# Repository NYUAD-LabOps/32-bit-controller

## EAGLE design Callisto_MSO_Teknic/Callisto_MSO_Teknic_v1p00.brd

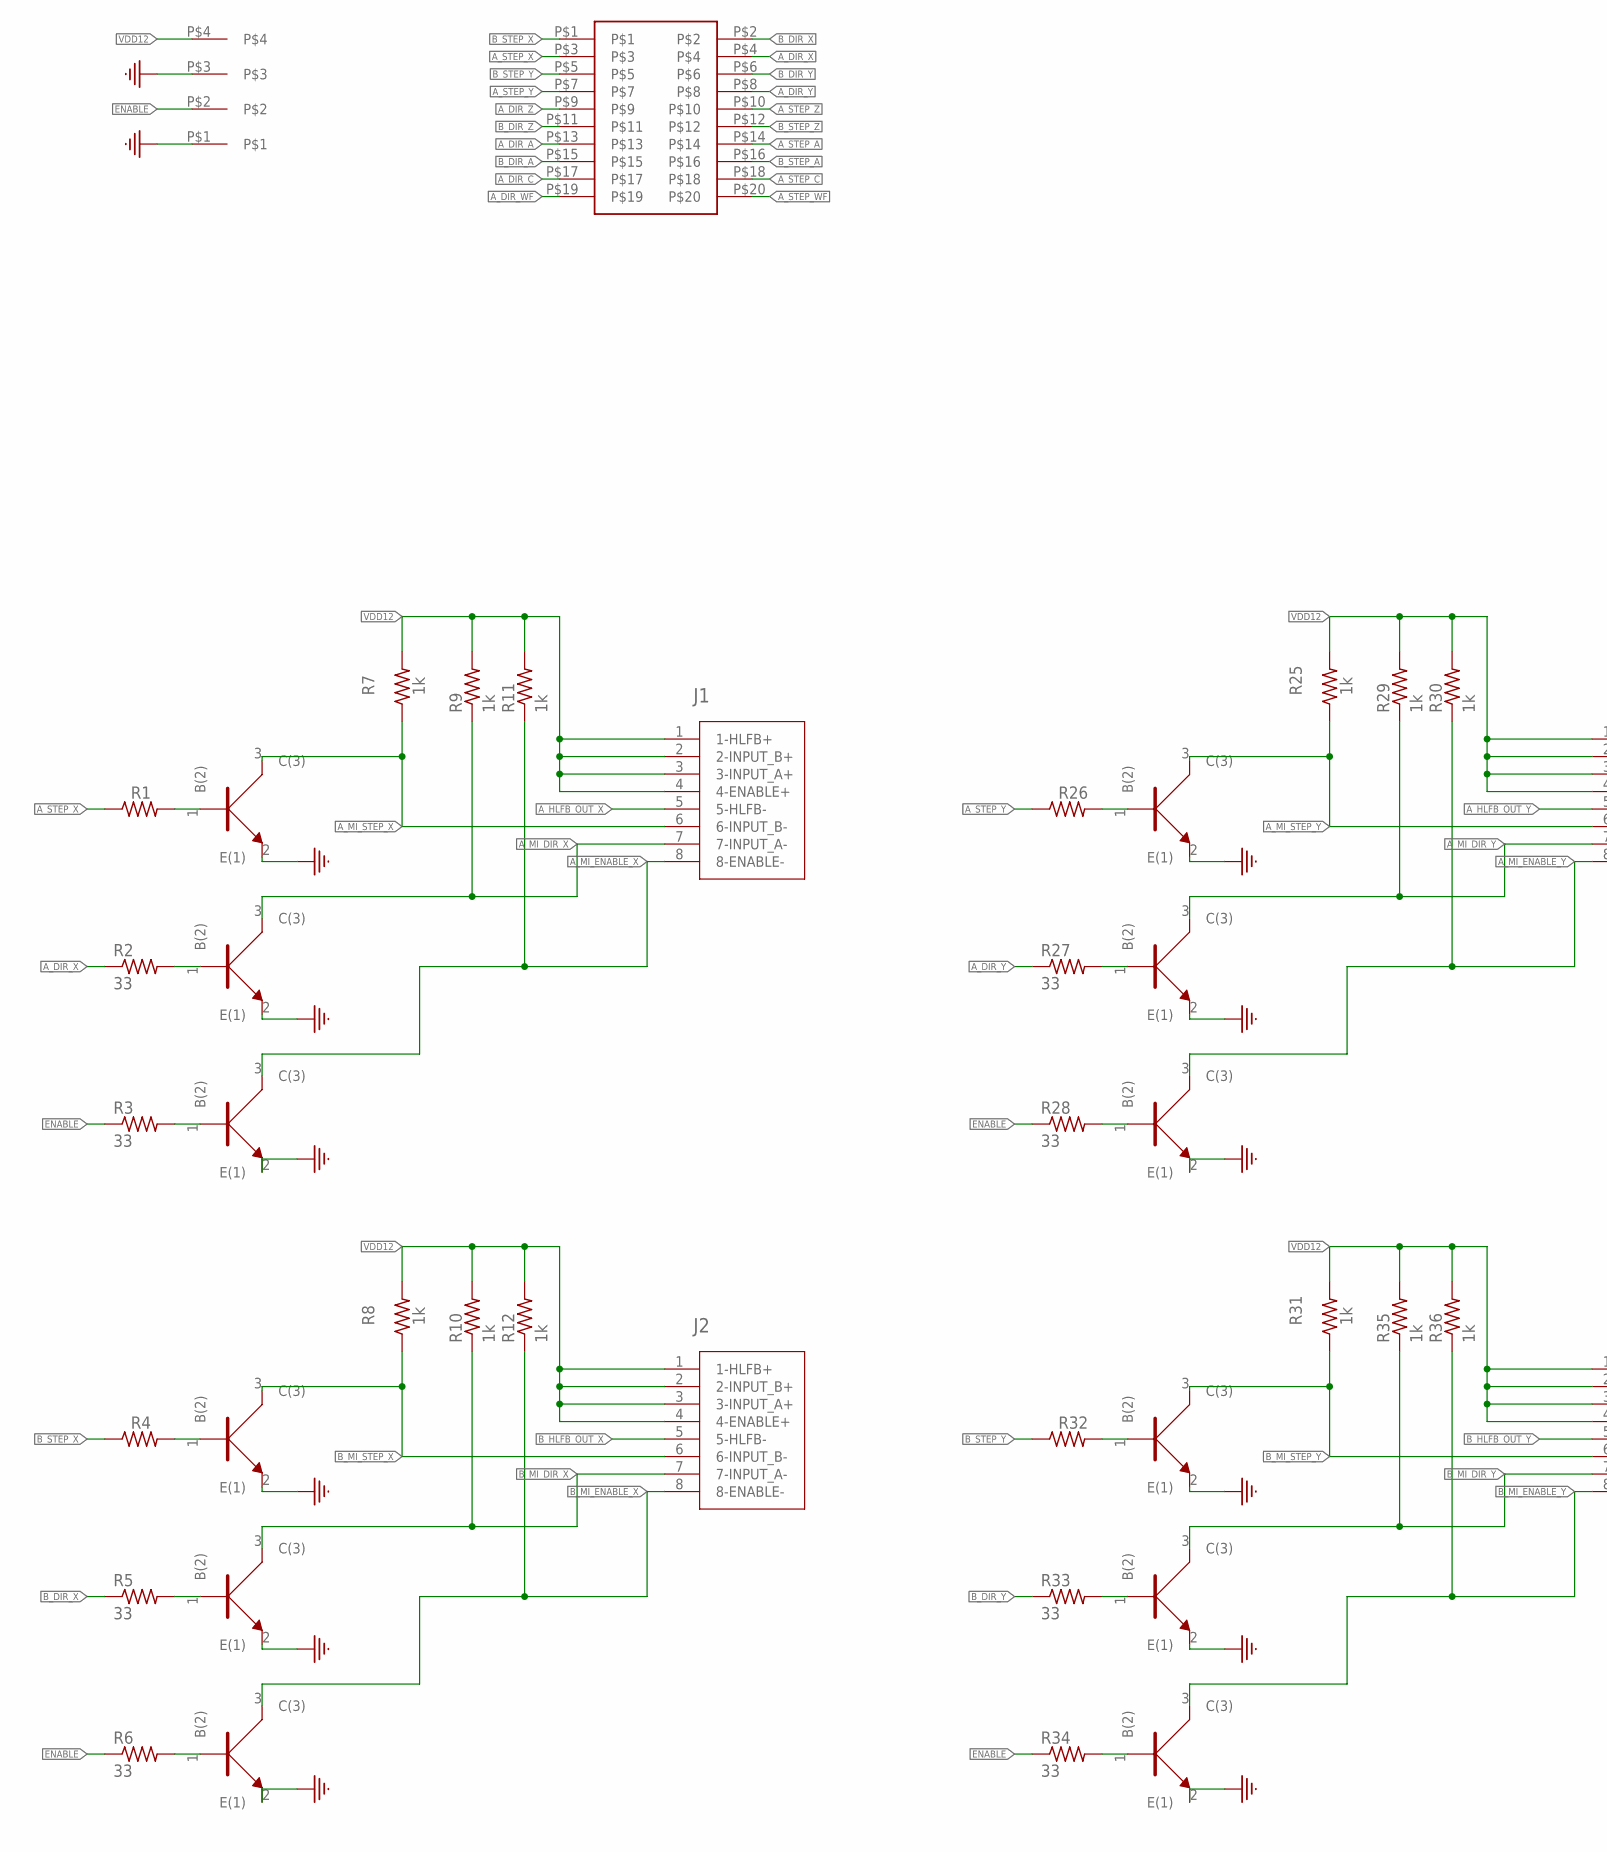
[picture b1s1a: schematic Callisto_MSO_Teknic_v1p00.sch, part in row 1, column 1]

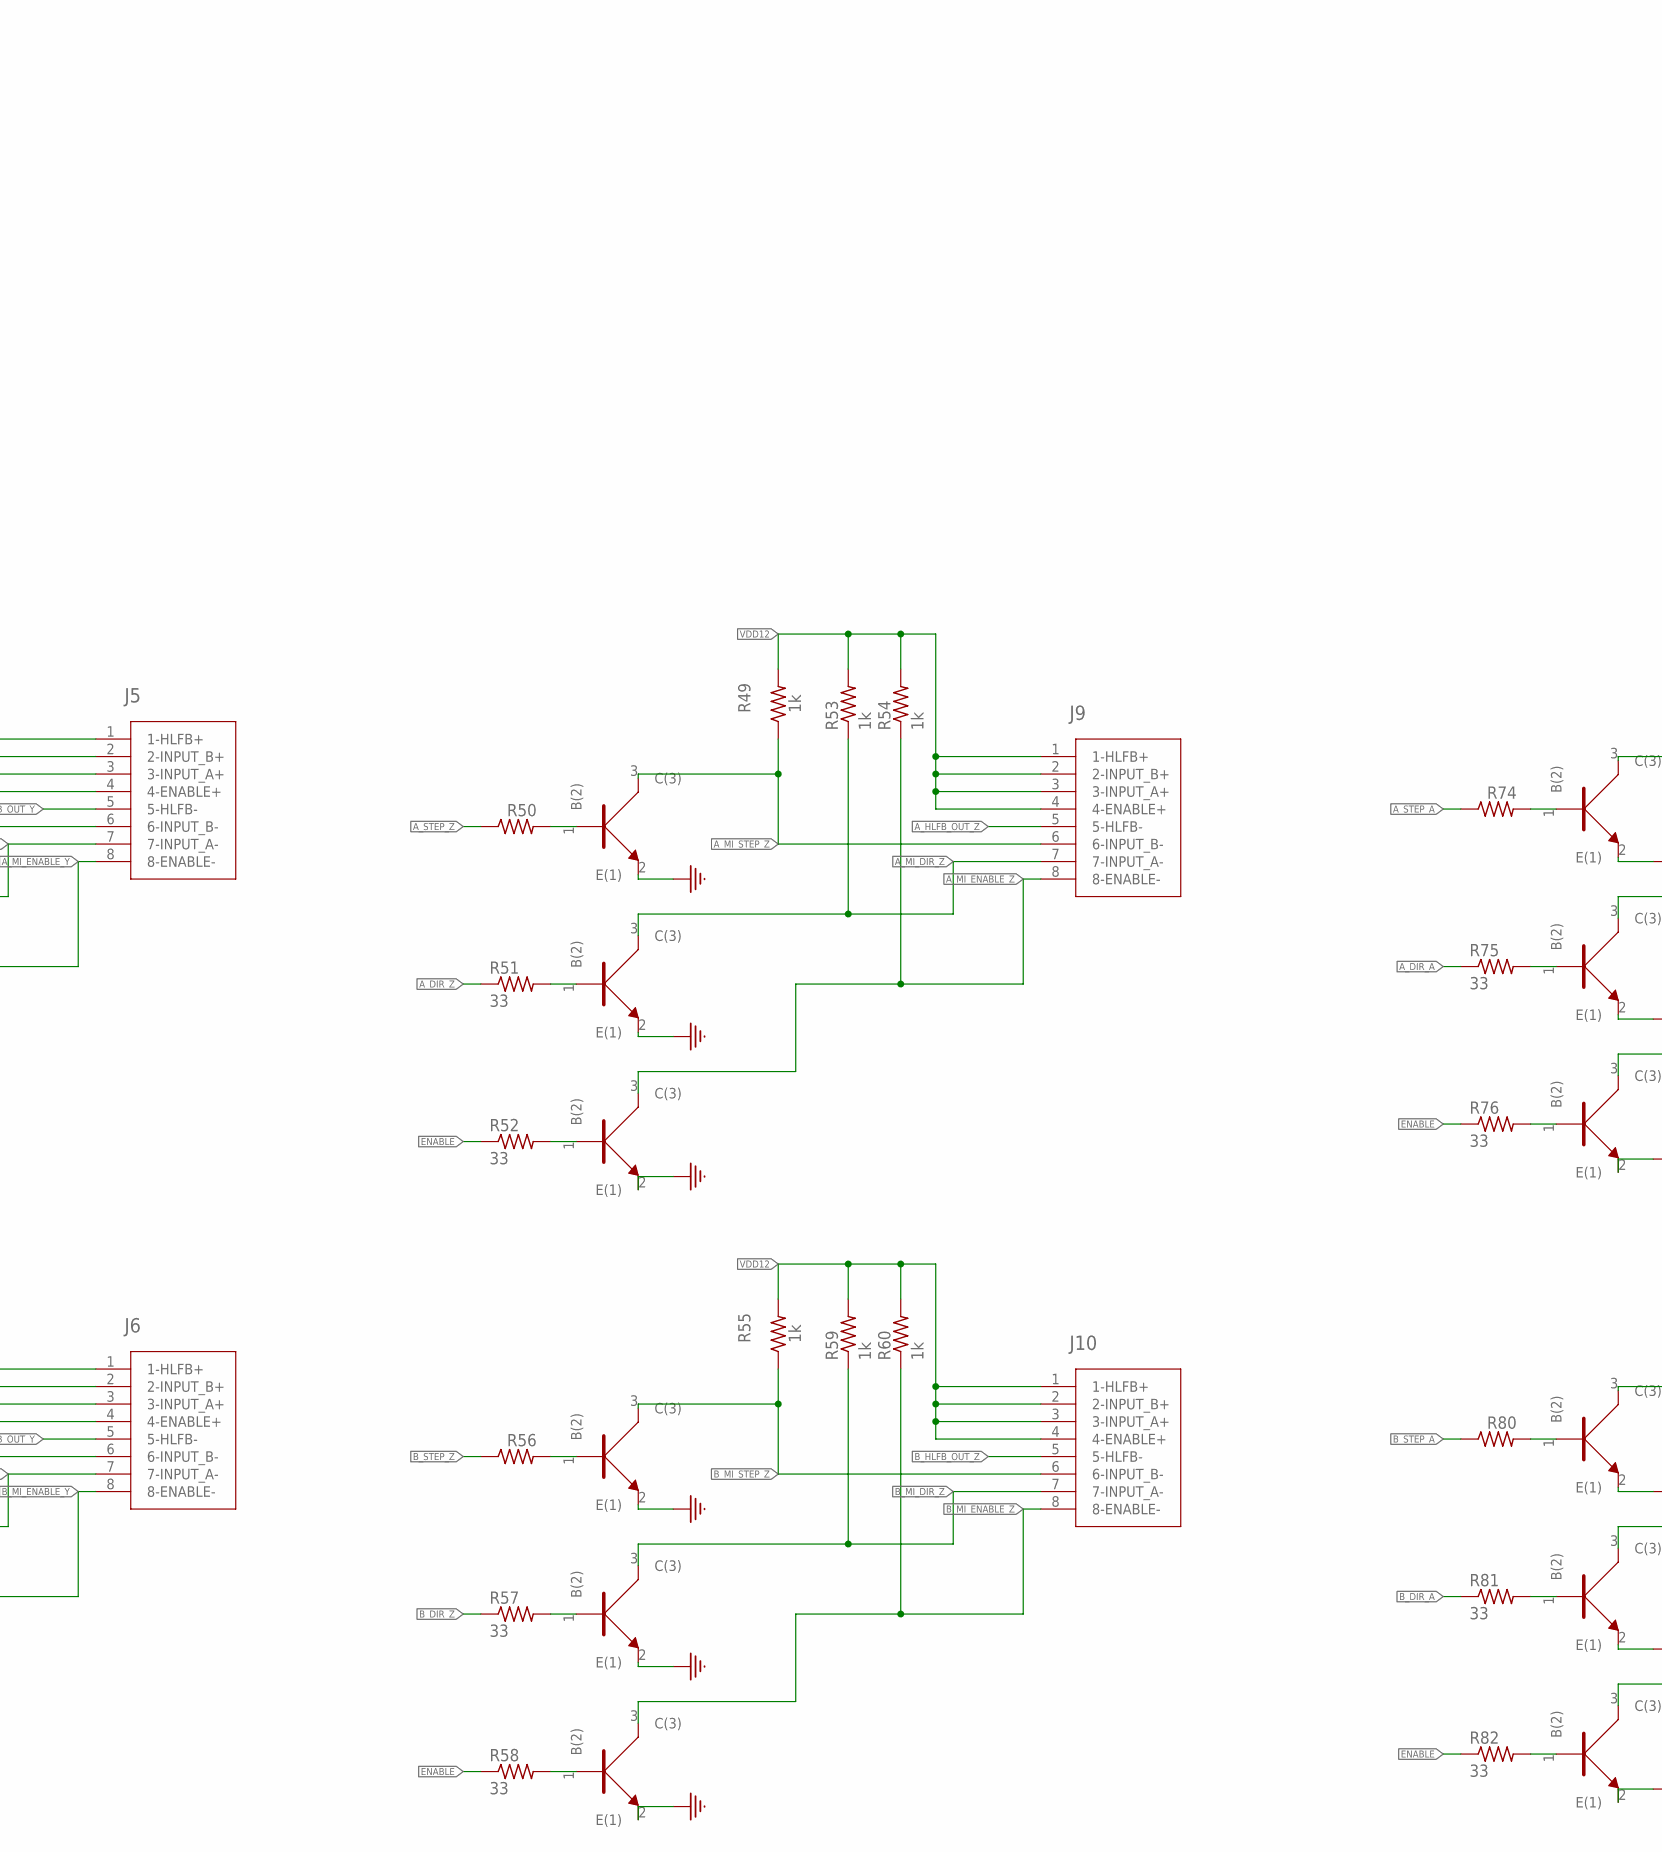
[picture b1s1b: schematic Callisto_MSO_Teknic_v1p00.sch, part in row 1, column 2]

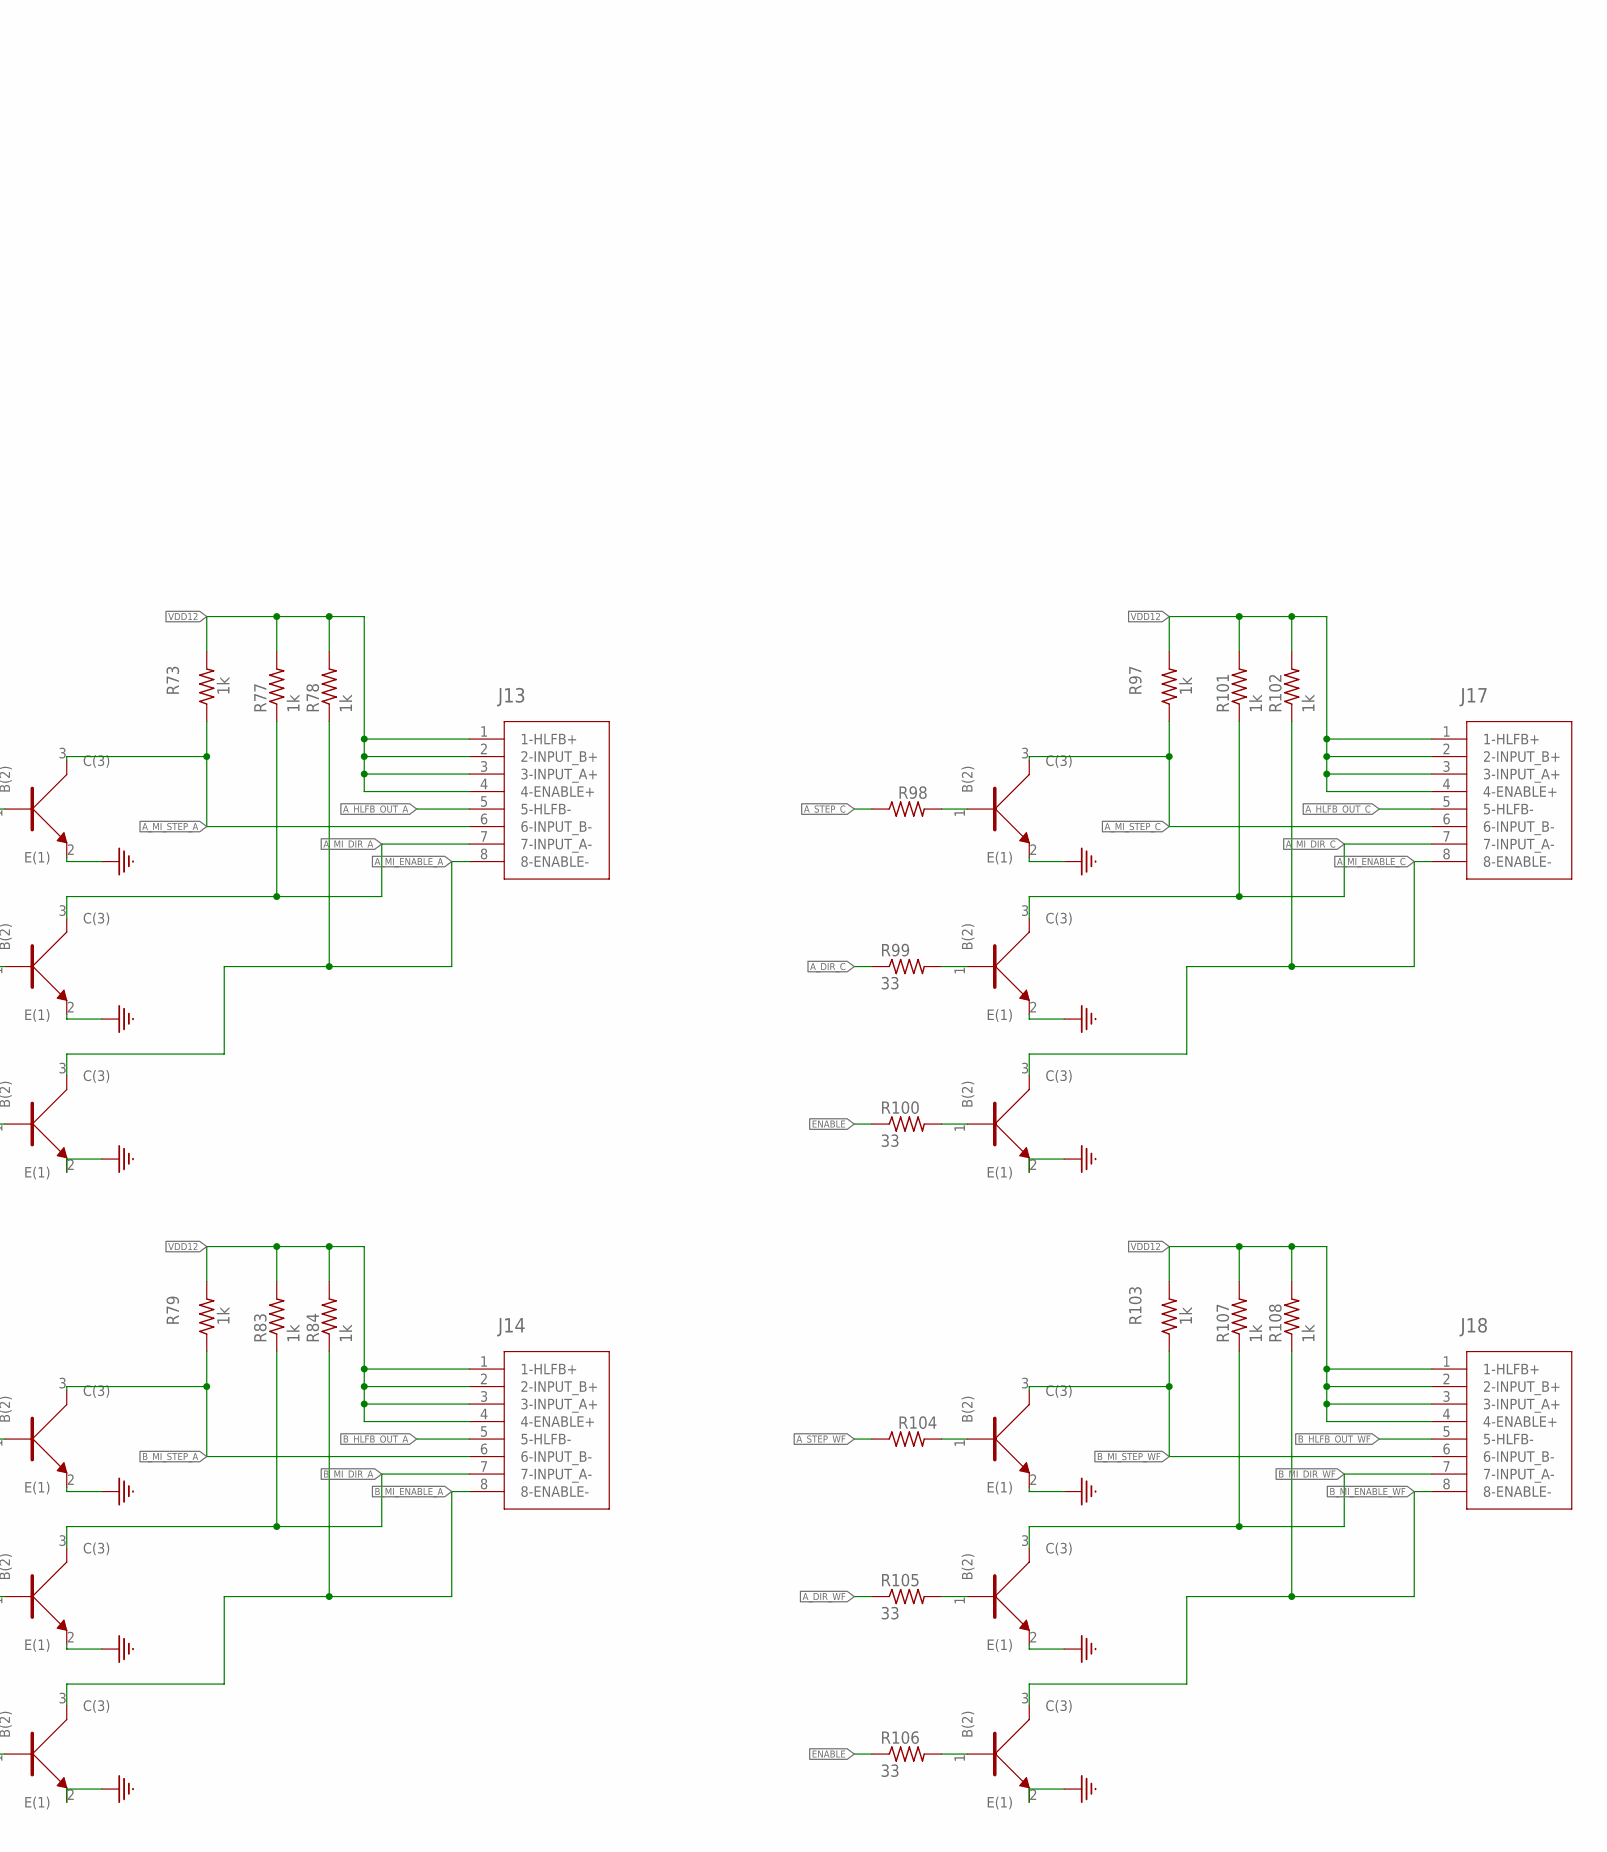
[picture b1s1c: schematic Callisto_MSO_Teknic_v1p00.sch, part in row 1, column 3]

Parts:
J1, J2, J5, J6, J9, J10, J13, J14, J17, J18: TEKNIC_8PIN_MOTOR; CON_39281083
J3: 2_X_10_HEADER_GENERIC2_X_10_.1_IN_RA; 2_X_10_.1_INCH
J7: 4-pos; 1X4_3.81MM_PITCH
R1, R2, R3, R4, R5, R6, R26, R27, R28, R32, R33, R34, R50, R51, R52, R56, R57, R58, R74, R75, R76, R80, R81, R82, R98, R99, R100, R104, R105, R106: 33; 0805
R7, R8, R9, R10, R11, R12, R25, R29, R30, R31, R35, R36, R49, R53, R54, R55, R59, R60, R73, R77, R78, R79, R83, R84, R97, R101, R102, R103, R107, R108: 1k; 0805
U1, U2, U3, U4, U5, U6, U13, U14, U15, U16, U17, U18, U25, U26, U27, U28, U29, U30, U37, U38, U39, U40, U41, U42, U49, U50, U51, U52, U53, U54: NPN; SOT323

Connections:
A_DIR_A: J3.P$13, R75.1
A_DIR_C: J3.P$17, R99.1
A_DIR_WF: J3.P$19, R105.1
A_DIR_X: J3.P$4, R2.1
A_DIR_Y: J3.P$8, R27.1
A_DIR_Z: J3.P$9, R51.1
A_HLFB_OUT_A: J13.5 (5-HLFB-)
A_HLFB_OUT_C: J17.5 (5-HLFB-)
A_HLFB_OUT_X: J1.5 (5-HLFB-)
A_HLFB_OUT_Y: J5.5 (5-HLFB-)
A_HLFB_OUT_Z: J9.5 (5-HLFB-)
A_MI_DIR_A: J13.7 (7-INPUT_A-), R77.1, U38.3 (C(3))
A_MI_DIR_C: J17.7 (7-INPUT_A-), R101.1, U50.3 (C(3))
A_MI_DIR_X: J1.7 (7-INPUT_A-), R9.1, U2.3 (C(3))
A_MI_DIR_Y: J5.7 (7-INPUT_A-), R29.1, U14.3 (C(3))
A_MI_DIR_Z: J9.7 (7-INPUT_A-), R53.1, U26.3 (C(3))
A_MI_ENABLE_A: J13.8 (8-ENABLE-), R78.1, U39.3 (C(3))
A_MI_ENABLE_C: J17.8 (8-ENABLE-), R102.1, U51.3 (C(3))
A_MI_ENABLE_X: J1.8 (8-ENABLE-), R11.1, U3.3 (C(3))
A_MI_ENABLE_Y: J5.8 (8-ENABLE-), R30.1, U15.3 (C(3))
A_MI_ENABLE_Z: J9.8 (8-ENABLE-), R54.1, U27.3 (C(3))
A_MI_STEP_A: J13.6 (6-INPUT_B-), R73.1, U37.3 (C(3))
A_MI_STEP_C: J17.6 (6-INPUT_B-), R97.1, U49.3 (C(3))
A_MI_STEP_X: J1.6 (6-INPUT_B-), R7.1, U1.3 (C(3))
A_MI_STEP_Y: J5.6 (6-INPUT_B-), R25.1, U13.3 (C(3))
A_MI_STEP_Z: J9.6 (6-INPUT_B-), R49.1, U25.3 (C(3))
A_STEP_A: J3.P$14, R74.1
A_STEP_C: J3.P$18, R98.1
A_STEP_WF: J3.P$20, R104.1
A_STEP_X: J3.P$3, R1.1
A_STEP_Y: J3.P$7, R26.1
A_STEP_Z: J3.P$10, R50.1
B_DIR_A: J3.P$15, R81.1
B_DIR_X: J3.P$2, R5.1
B_DIR_Y: J3.P$6, R33.1
B_DIR_Z: J3.P$11, R57.1
B_HLFB_OUT_A: J14.5 (5-HLFB-)
B_HLFB_OUT_WF: J18.5 (5-HLFB-)
B_HLFB_OUT_X: J2.5 (5-HLFB-)
B_HLFB_OUT_Y: J6.5 (5-HLFB-)
B_HLFB_OUT_Z: J10.5 (5-HLFB-)
B_MI_DIR_A: J14.7 (7-INPUT_A-), R83.1, U41.3 (C(3))
B_MI_DIR_WF: J18.7 (7-INPUT_A-), R107.1, U53.3 (C(3))
B_MI_DIR_X: J2.7 (7-INPUT_A-), R10.1, U5.3 (C(3))
B_MI_DIR_Y: J6.7 (7-INPUT_A-), R35.1, U17.3 (C(3))
B_MI_DIR_Z: J10.7 (7-INPUT_A-), R59.1, U29.3 (C(3))
B_MI_ENABLE_A: J14.8 (8-ENABLE-), R84.1, U42.3 (C(3))
B_MI_ENABLE_WF: J18.8 (8-ENABLE-), R108.1, U54.3 (C(3))
B_MI_ENABLE_X: J2.8 (8-ENABLE-), R12.1, U6.3 (C(3))
B_MI_ENABLE_Y: J6.8 (8-ENABLE-), R36.1, U18.3 (C(3))
B_MI_ENABLE_Z: J10.8 (8-ENABLE-), R60.1, U30.3 (C(3))
B_MI_STEP_A: J14.6 (6-INPUT_B-), R79.1, U40.3 (C(3))
B_MI_STEP_WF: J18.6 (6-INPUT_B-), R103.1, U52.3 (C(3))
B_MI_STEP_X: J2.6 (6-INPUT_B-), R8.1, U4.3 (C(3))
B_MI_STEP_Y: J6.6 (6-INPUT_B-), R31.1, U16.3 (C(3))
B_MI_STEP_Z: J10.6 (6-INPUT_B-), R55.1, U28.3 (C(3))
B_STEP_A: J3.P$16, R80.1
B_STEP_X: J3.P$1, R4.1
B_STEP_Y: J3.P$5, R32.1
B_STEP_Z: J3.P$12, R56.1
ENABLE: J7.P$2, R3.1, R6.1, R28.1, R34.1, R52.1, R58.1, R76.1, R82.1, R100.1, R106.1
GND: J7.P$1, J7.P$3, U1.2 (E(1)), U2.2 (E(1)), U3.2 (E(1)), U4.2 (E(1)), U5.2 (E(1)), U6.2 (E(1)), U13.2 (E(1)), U14.2 (E(1)), U15.2 (E(1)), U16.2 (E(1)), U17.2 (E(1)), U18.2 (E(1)), U25.2 (E(1)), U26.2 (E(1)), U27.2 (E(1)), U28.2 (E(1)), U29.2 (E(1)), U30.2 (E(1)), U37.2 (E(1)), U38.2 (E(1)), U39.2 (E(1)), U40.2 (E(1)), U41.2 (E(1)), U42.2 (E(1)), U49.2 (E(1)), U50.2 (E(1)), U51.2 (E(1)), U52.2 (E(1)), U53.2 (E(1)), U54.2 (E(1))
unnamed: R2.2, U2.1 (B(2))
unnamed: R1.2, U1.1 (B(2))
unnamed: R3.2, U3.1 (B(2))
unnamed: R5.2, U5.1 (B(2))
unnamed: R6.2, U6.1 (B(2))
unnamed: R4.2, U4.1 (B(2))
unnamed: R27.2, U14.1 (B(2))
unnamed: R28.2, U15.1 (B(2))
unnamed: R26.2, U13.1 (B(2))
unnamed: R33.2, U17.1 (B(2))
unnamed: R34.2, U18.1 (B(2))
unnamed: R32.2, U16.1 (B(2))
unnamed: R51.2, U26.1 (B(2))
unnamed: R52.2, U27.1 (B(2))
unnamed: R50.2, U25.1 (B(2))
unnamed: R57.2, U29.1 (B(2))
unnamed: R58.2, U30.1 (B(2))
unnamed: R56.2, U28.1 (B(2))
unnamed: R75.2, U38.1 (B(2))
unnamed: R76.2, U39.1 (B(2))
unnamed: R74.2, U37.1 (B(2))
unnamed: R81.2, U41.1 (B(2))
unnamed: R82.2, U42.1 (B(2))
unnamed: R80.2, U40.1 (B(2))
unnamed: R99.2, U50.1 (B(2))
unnamed: R100.2, U51.1 (B(2))
unnamed: R98.2, U49.1 (B(2))
unnamed: R105.2, U53.1 (B(2))
unnamed: R106.2, U54.1 (B(2))
unnamed: R104.2, U52.1 (B(2))
VDD12: J1.1 (1-HLFB+), J1.2 (2-INPUT_B+), J1.3 (3-INPUT_A+), J1.4 (4-ENABLE+), J2.1 (1-HLFB+), J2.2 (2-INPUT_B+), J2.3 (3-INPUT_A+), J2.4 (4-ENABLE+), J5.1 (1-HLFB+), J5.2 (2-INPUT_B+), J5.3 (3-INPUT_A+), J5.4 (4-ENABLE+), J6.1 (1-HLFB+), J6.2 (2-INPUT_B+), J6.3 (3-INPUT_A+), J6.4 (4-ENABLE+), J7.P$4, J9.1 (1-HLFB+), J9.2 (2-INPUT_B+), J9.3 (3-INPUT_A+), J9.4 (4-ENABLE+), J10.1 (1-HLFB+), J10.2 (2-INPUT_B+), J10.3 (3-INPUT_A+), J10.4 (4-ENABLE+), J13.1 (1-HLFB+), J13.2 (2-INPUT_B+), J13.3 (3-INPUT_A+), J13.4 (4-ENABLE+), J14.1 (1-HLFB+), J14.2 (2-INPUT_B+), J14.3 (3-INPUT_A+), J14.4 (4-ENABLE+), J17.1 (1-HLFB+), J17.2 (2-INPUT_B+), J17.3 (3-INPUT_A+), J17.4 (4-ENABLE+), J18.1 (1-HLFB+), J18.2 (2-INPUT_B+), J18.3 (3-INPUT_A+), J18.4 (4-ENABLE+), R7.2, R8.2, R9.2, R10.2, R11.2, R12.2, R25.2, R29.2, R30.2, R31.2, R35.2, R36.2, R49.2, R53.2, R54.2, R55.2, R59.2, R60.2, R73.2, R77.2, R78.2, R79.2, R83.2, R84.2, R97.2, R101.2, R102.2, R103.2, R107.2, R108.2

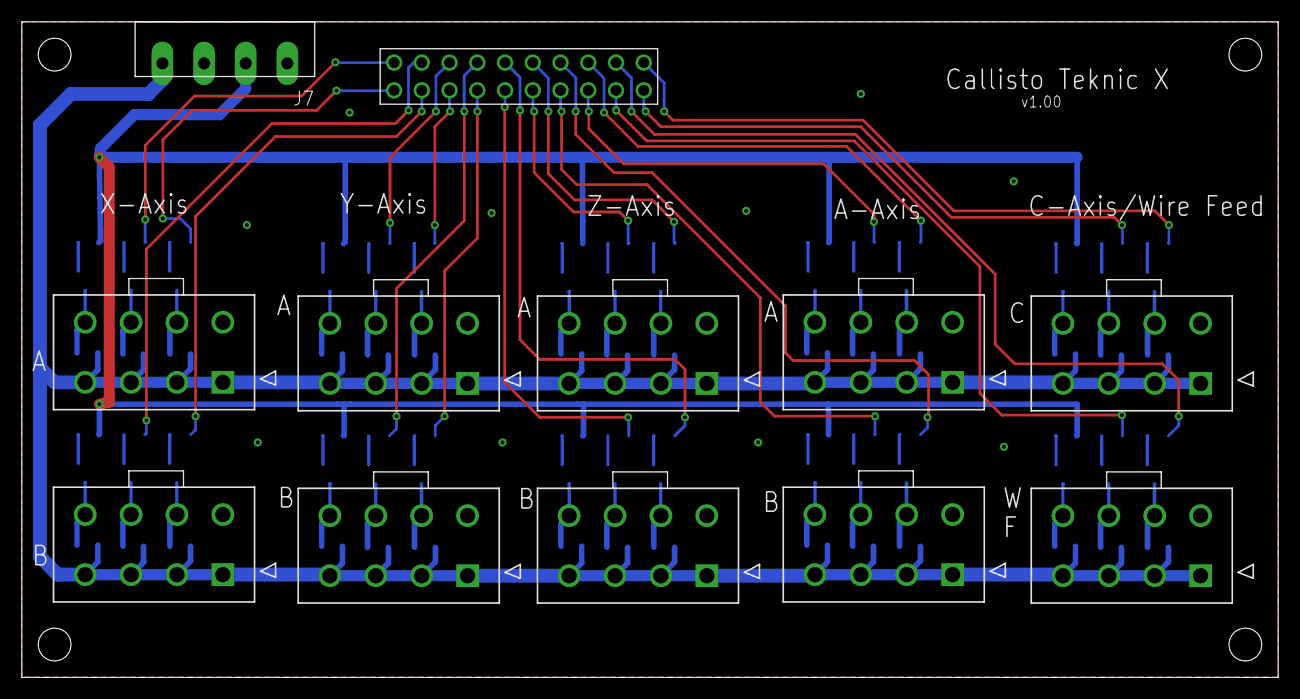
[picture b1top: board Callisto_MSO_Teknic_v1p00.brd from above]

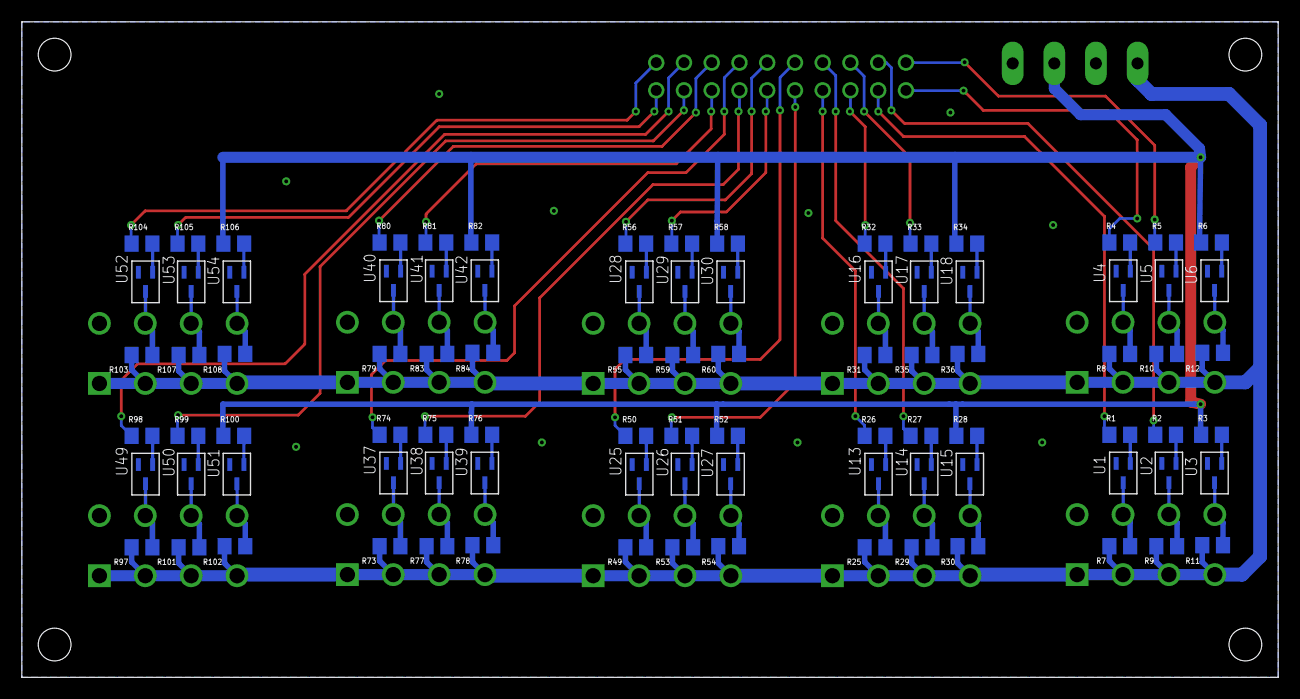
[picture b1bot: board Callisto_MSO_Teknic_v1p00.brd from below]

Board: 2 copper layers, 115.0 x 60.0 mm, 102 parts (90 on the bottom side), 83 nets.

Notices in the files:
parts and their libraries:
COPYRIGHT: Copyright (C) 2022 Ultra Librarian. All rights reserved.
COPYRIGHT: Copyright (C) 2018 Accelerated Designs. All rights reserved
